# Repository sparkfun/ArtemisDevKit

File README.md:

SparkFun Artemis Development Kit
========================================

* [*SparkFun Artemis Development Kit (DEV-16828)*](https://www.sparkfun.com/products/16828)
* [*SparkFun Artemis Development Kit with Camera (KIT-17071)*](https://www.sparkfun.com/products/17071)

The [*SparkFun Artemis Development Kit (DEV-16828)*](https://www.sparkfun.com/products/16828) is the latest board to be released around the SparkFun Artemis Module and it allows access to more software development features than previous Artemis based boards. Recommended software used to program the Artemis DK are the Arduino IDE, Arm® Mbed™ OS (Studio and CLI), and AmbiqSDK. An updated USB interface (MKL26Z128VFM4 Arm® Cortex®-M0+ MCU, from NXP) allows the Artemis Dev Kit to act as:

* Mass Storage Device (MSD): Used to provide drag and drop programming to the Artemis Module.
* Human Interface Device (HID): Used for the debugging interface to the Artemis Module.
* Communication Port (COM): Used to provide a serial communication UART between the Artemis and the USB connection (PC).

Repository Contents
-------------------

* **/Hardware**
   * Eagle design files (.brd, .sch)
   * Dimensions (.pdf and .png)
   * **/Production** - Production panel files (.brd)
* **/Reference**
   * Datasheets (.pdf)
   * Functional Block Digaram (.png)

Documentation
--------------
* [Hardware Getting Started Guide](https://learn.sparkfun.com/tutorials/1198) - Basic Hardware Guide for the Artemis DK
* Software Guides:
    * [Artemis Development with the Arduino IDE](https://learn.sparkfun.com/tutorials/artemis-development-with-the-arduino-ide) - A software guide for developing with the Artemis module (and related boards) in the Arduino IDE
    * [Artemis Development with Arm&reg; Mbed&trade; OS (Beta)](https://learn.sparkfun.com/tutorials/artemis-development-on-arm-mbed-os-beta) - A software pre-release guide to get started developing in with Mbed&trade; OS
    * Artemis Development with Arm&reg; Mbed&trade; OS (Pending release)
    * [Artemis Development with the AmbiqSDK](https://learn.sparkfun.com/tutorials/using-sparkfun-edge-board-with-ambiq-apollo3-sdk) - A software guide for utilizing the SparkFun Edge board with the AmbiqSDK
* [GitHub Repository for Apollo3 Board Support Packages (BSP)](https://github.com/sparkfun/SparkFun_Apollo3_AmbiqSuite_BSPs) - The Board Support Packages (BSPs) for SparkFun Apollo3 (Artemis) based boards to be used in the AmbiqSuite SDK
    * [ DAPLink Bootloader: `kl26z_artemis_dk_if.bin`](https://github.com/sparkfun/SparkFun_Apollo3_AmbiqSuite_BSPs/raw/master/artemis_dk/intfc/kl26z_bl.bin) - Underlying *bootloader* firmware for the MKL26Z MCU
    * [DAPLink Interface Firmware: `kl26z_bl.bin`](https://github.com/sparkfun/SparkFun_Apollo3_AmbiqSuite_BSPs/raw/master/artemis_dk/intfc/kl26z_artemis_dk_if.bin) - The accompanying *interface firmware* for the DAPLink debug probes from the MKL26Z to the target Artemis Module
* Development Software:
    * [SparkFun Ambiq Apollo3 Arduino Core](https://github.com/sparkfun/Arduino_Apollo3) - The SparkFun Arduino core for the Apollo3 MCU (i.e. the Artemis modules)
        * `.json` file needed for the SparkFun Ambiq Apollo3 Arduino Core:
        <br>
            <code><a href="https://raw.githubusercontent.com/sparkfun/Arduino_Apollo3/master/package_sparkfun_apollo3_index.json">https://raw.githubusercontent.com/sparkfun/Arduino_Apollo3/master/package_sparkfun_apollo3_index.json</a></code>
    * [Mbed™ OS](https://github.com/sparkfun/mbed-os-ambiq-apollo3) - Implementation of the Apollo3 (i.e. Artemis module) in Mbed&trade; OS
    * [AmbiqSDK](https://github.com/sparkfun/AmbiqSuiteSDK) - A copy of the AmbiqSuite SDK maintained by SparkFun
    * [pyOCD](https://github.com/sparkfun/pyOCD) - Implementation of the Apollo3 (i.e. Artemis module) for pyOCD
* Arduino Libraries:
    * [SparkFun LIS2DH12 Arduino Library](https://github.com/sparkfun/SparkFun_LIS2DH12_Arduino_Library) - The Arduino library for the accelerometer
    * [ArduinoBLE Library](https://github.com/arduino-libraries/ArduinoBLE) - The Arduino library for the BLE support

Product Versions
----------------
* [*SparkFun Artemis Development Kit with Camera (KIT-17071)*](https://www.sparkfun.com/products/17071) - v1.0 Initial Release *(kitted with Himax Camera)*
* [*SparkFun Artemis Development Kit (DEV-16828)*](https://www.sparkfun.com/products/16828) - v1.0 Initial Release

License Information
-------------------

This product is _**open source**_! 

Please review the LICENSE.md file for license information. 

If you have any questions or concerns on licensing, please contact technical support on our [SparkFun forums](https://forum.sparkfun.com/viewforum.php?f=152).

Distributed as-is; no warranty is given.

- Your friends at SparkFun.

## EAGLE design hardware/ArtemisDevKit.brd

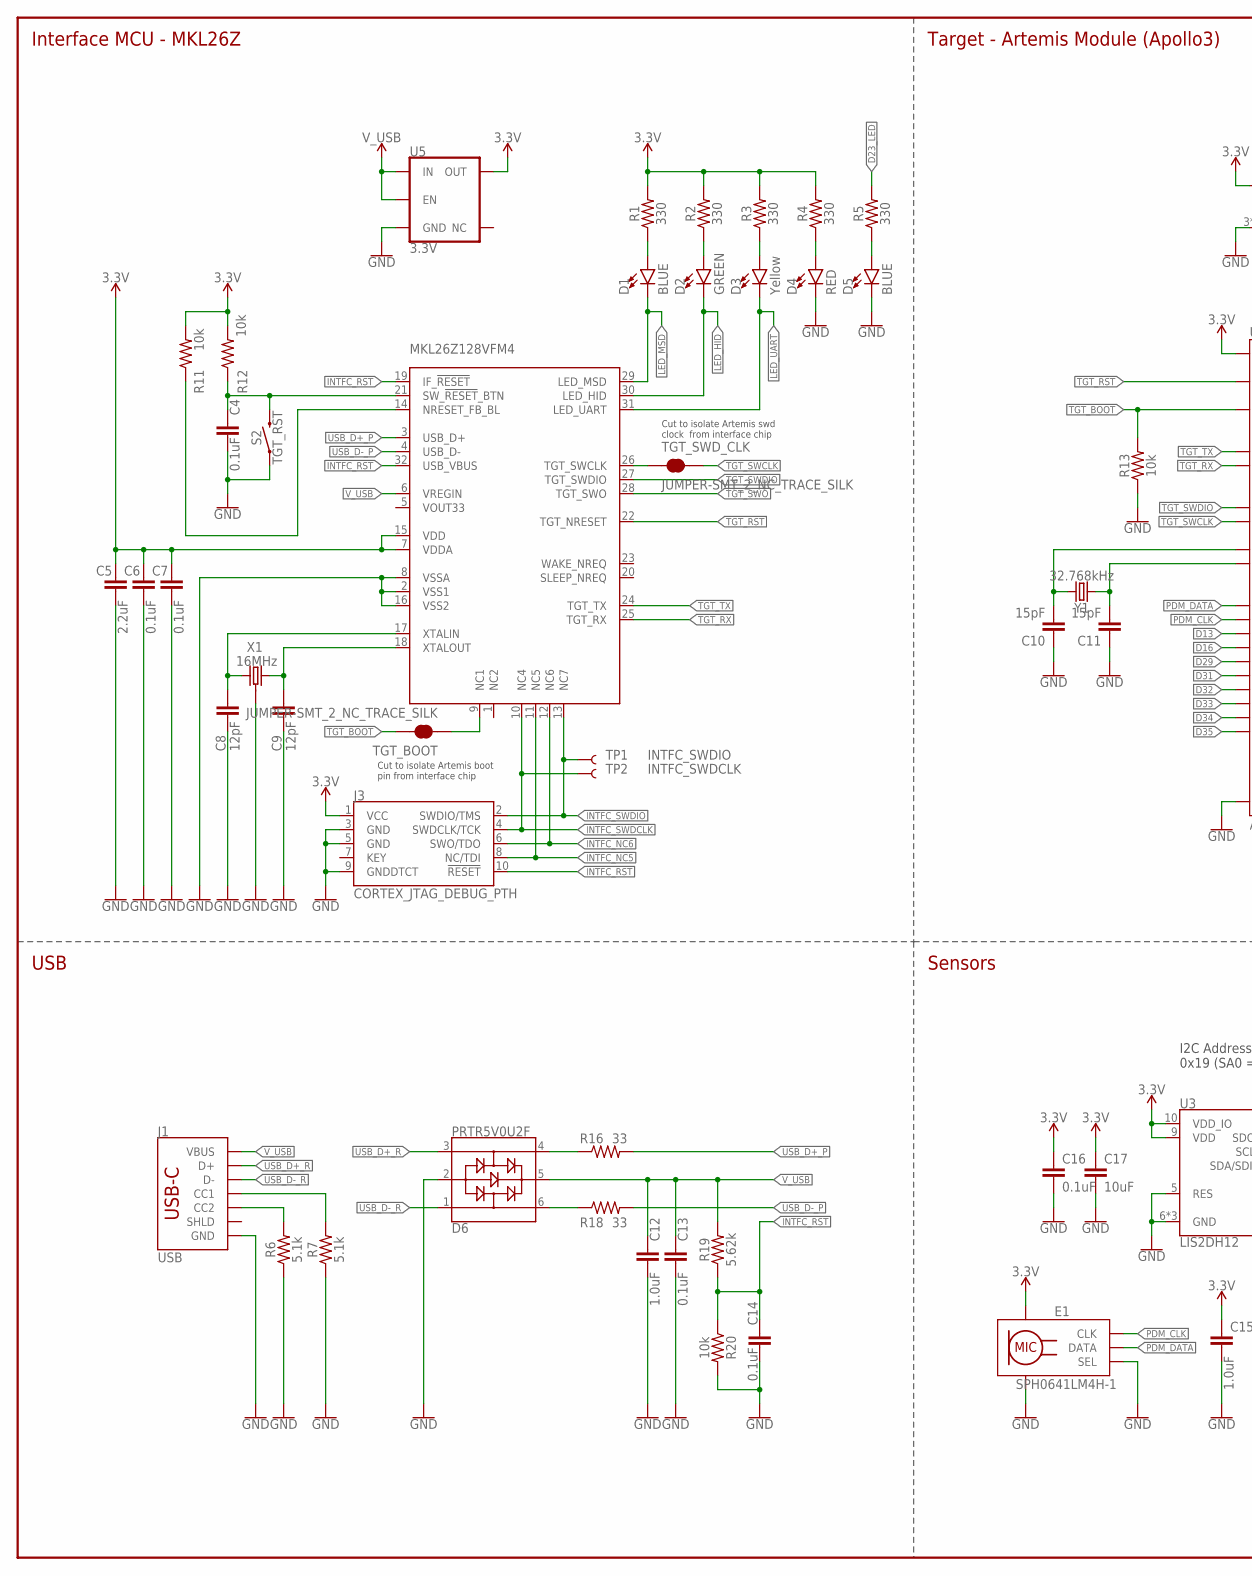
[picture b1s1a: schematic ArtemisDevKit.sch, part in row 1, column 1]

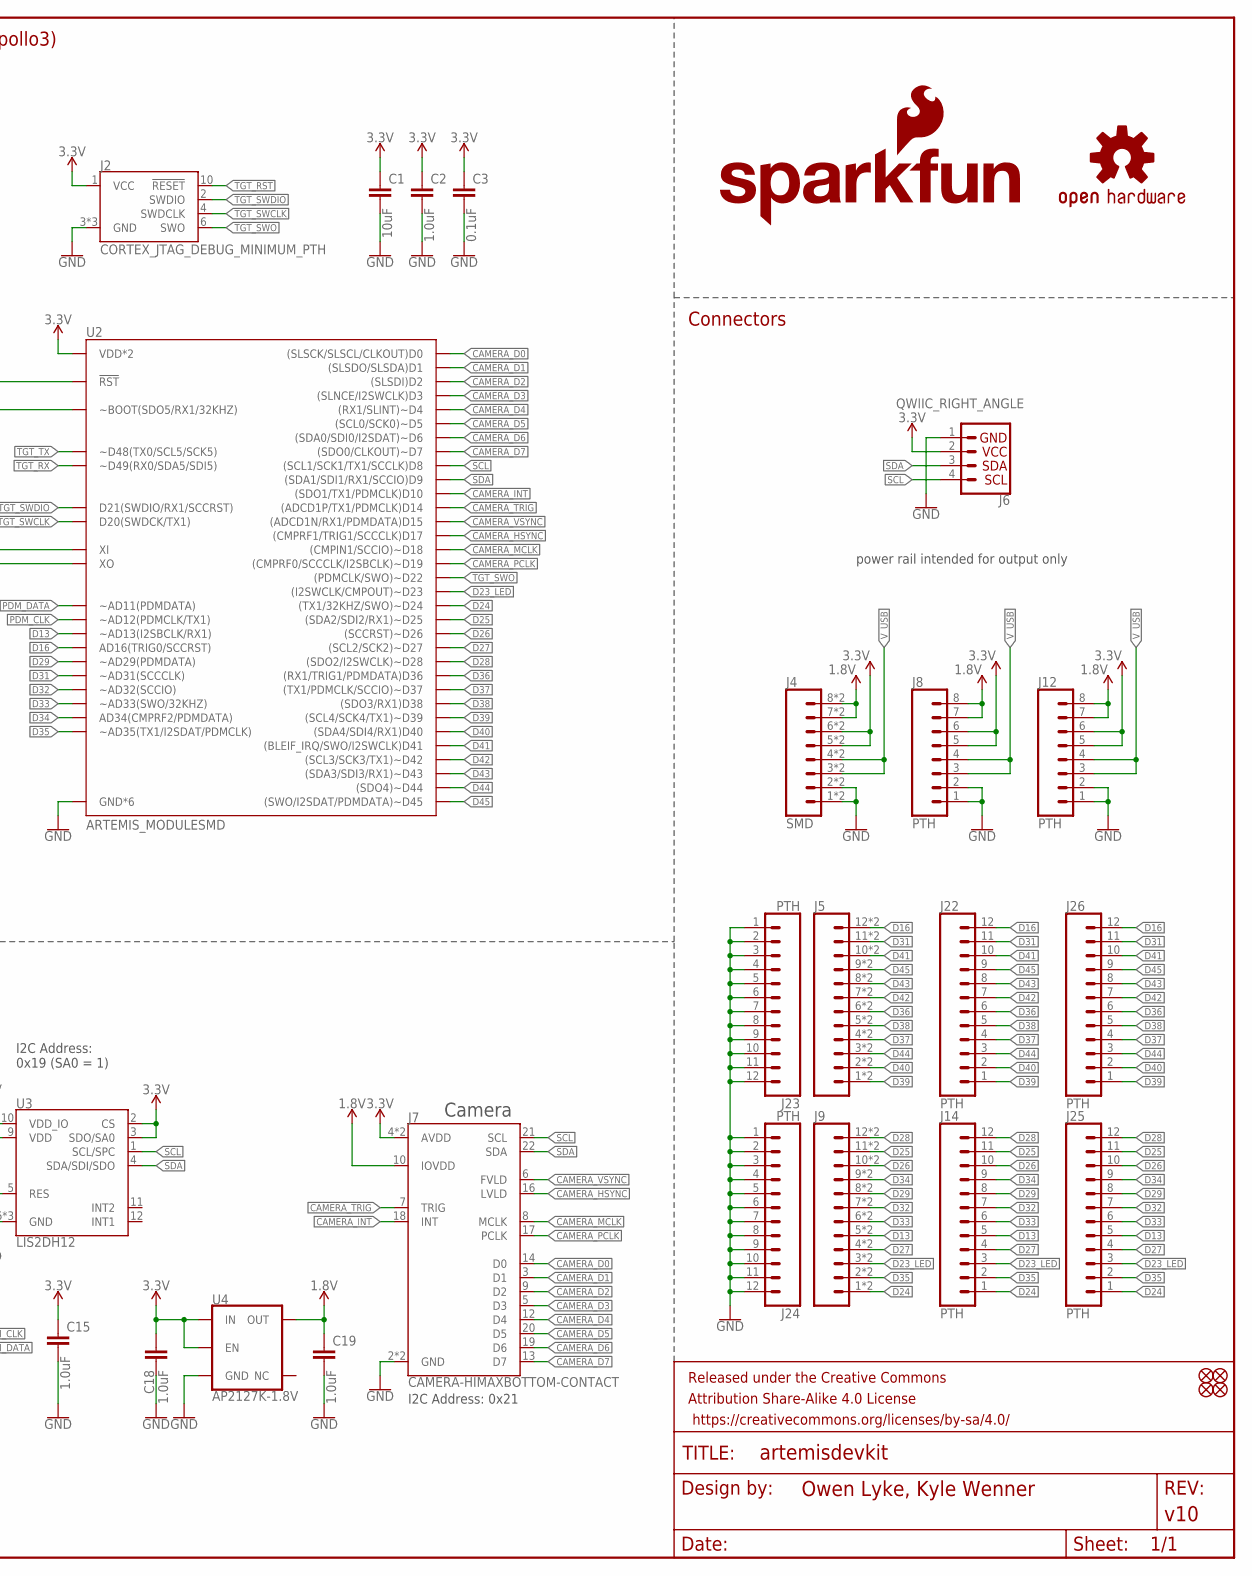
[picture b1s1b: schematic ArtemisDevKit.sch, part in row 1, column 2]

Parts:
C1, C17: 10uF; 0603
C2, C12, C15, C18, C19: 1.0uF; 0603
C3, C4, C6, C7, C13, C14, C16: 0.1uF; 0603
C5: 2.2uF; 0603
C8, C9: 12pF; 0603
C10, C11: 15pF; 0603
D1, D5: BLUE; LED-0603
D2: GREEN; LED-0603
D3: Yellow; LED-0603
D4: RED; LED-0603
D6: PRTR5V0U2F; SOT886
E1: SPH0641LM4H-1; SPH0641LM4H-1_MICROPHONE
FD1, FD2, FD3, FD4: FIDUCIAL1X2; FIDUCIAL-1X2
FRAME1: FRAME-LEDGER; CREATIVE_COMMONS
J1: USB; USB-C-16P
J2: CORTEX_JTAG_DEBUG_MINIMUM_PTH; 2X5-PTH-1.27MM
J3: CORTEX_JTAG_DEBUG_PTH; 2X5-PTH-1.27MM
J4: SMD; 1X08_SMD_COMBINED
J5, J9: CONN_12SMD_COMBINED; 1X12_SMD_COMBINED
J6: QWIIC_RIGHT_ANGLE; JST04_1MM_RA
J7: CAMERA-HIMAXBOTTOM-CONTACT; FPC-24-AMPHENOL-SFV24R-1STE1HLF
J8, J12: PTH; 1X08_NO_SILK
J14, J22, J23, J24, J25, J26: PTH; 1X12_NO_SILK
LOGO1: OSHW-LOGOS; OSHW-LOGO-S
LOGO2: SFE_LOGO_NAME_FLAME.2_INCH; SFE_LOGO_NAME_FLAME_.2
R1, R2, R3, R4, R5: 330; 0603
R6, R7: 5.1k; 0603
R11, R12, R13, R20: 10k; 0603
R16, R18: 33; 0603
R19: 5.62k; 0603
S2: TGT_RST; TACTILE_SWITCH_SMD_5.2MM
TGT_BOOT: JUMPER-SMT_2_NC_TRACE_SILK; SMT-JUMPER_2_NC_TRACE_SILK
TGT_SWD_CLK: JUMPER-SMT_2_NC_TRACE_SILK; SMT-JUMPER_2_NC_TRACE_SILK
TP1: INTFC_SWDIO; PAD.03X.03
TP2: INTFC_SWDCLK; PAD.03X.03
U1: DAPLINK_KL26Z128VFM4; QFN-32-NOPAD
U2: ARTEMIS_MODULESMD; ARTEMIS_FP
U3: LIS2DH12; LGA-12-LISDH12
U4: AP2127K-1.8V; SOT23-5
U5: 3.3V; SOT23-5
X1: 16MHz; CRYSTAL-SMD-2X2.5MM
Y1: 32.768kHz; CRYSTAL-SMD-3.2X1.5MM

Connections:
1.8V: C19.1, J4.7, J4.7@2 (7), J4.8, J4.8@2 (8), J7.10 (IOVDD), J8.7, J8.8, J12.7, J12.8, U4.5 (OUT)
3.3V: C1.1, C2.1, C3.1, C5.1, C6.1, C7.1, C15.1, C16.1, C17.1, C18.1, E1.5 (VDD), J2.1 (VCC), J3.1 (VCC), J4.5, J4.5@2 (5), J4.6, J4.6@2 (6), J6.2, J7.4 (AVDD), J7.11 (AVDD), J8.5, J8.6, J12.5, J12.6, R1.2, R2.2, R3.2, R4.2, R11.2, R12.2, U1.7 (VDDA), U1.15 (VDD), U2.VDD@36 (VDD*2), U2.VDD@37 (VDD*2), U3.2 (CS), U3.3 (SDO/SA0), U3.9 (VDD), U3.10 (VDD_IO), U4.1 (IN), U4.3 (EN), U5.5 (OUT)
!INTFC_RST: C14.1, J3.10 (!RESET), R19.1, R20.1, U1.19 (IF_!RESET), U1.32 (USB_VBUS)
!RST!_BTN: C4.1, R12.1, S2.3 (2), U1.21 (SW_!RESET!_BTN)
!TGT_RST: J2.10 (!RESET), U1.22 (TGT_NRESET), U2.~RST (!RST)
CAMERA_D0: J7.14 (D0), U2.D0 ((SLSCK/SLSCL/CLKOUT)D0)
CAMERA_D1: J7.3 (D1), U2.D1 ((SLSDO/SLSDA)D1)
CAMERA_D2: J7.9 (D2), U2.D2 ((SLSDI)D2)
CAMERA_D3: J7.5 (D3), U2.D3 ((SLNCE/I2SWCLK)D3)
CAMERA_D4: J7.12 (D4), U2.~D4 ((RX1/SLINT)~D4)
CAMERA_D5: J7.20 (D5), U2.~D5 ((SCL0/SCK0)~D5)
CAMERA_D6: J7.19 (D6), U2.~D6 ((SDA0/SDI0/I2SDAT)~D6)
CAMERA_D7: J7.13 (D7), U2.D7 ((SDO0/CLKOUT)~D7)
CAMERA_HSYNC: J7.16 (LVLD), U2.D17 ((CMPRF1/TRIG1/SCCCLK)D17)
CAMERA_INT: J7.18 (INT), U2.D10 ((SDO1/TX1/PDMCLK)D10)
CAMERA_MCLK: J7.8 (MCLK), U2.~D18 ((CMPIN1/SCCIO)~D18)
CAMERA_PCLK: J7.17 (PCLK), U2.~D19 ((CMPRF0/SCCCLK/I2SBCLK)~D19)
CAMERA_TRIG: J7.7 (TRIG), U2.D14 ((ADCD1P/TX1/PDMCLK)D14)
CAMERA_VSYNC: J7.6 (FVLD), U2.D15 ((ADCD1N/RX1/PDMDATA)D15)
D13: J9.5, J9.5@2 (5), J14.5, J25.5, U2.~AD13 (~AD13(I2SBCLK/RX1))
D16: J5.12, J5.12@2 (12), J22.12, J26.12, U2.AD16 (AD16(TRIG0/SCCRST))
D23_LED: J9.3, J9.3@2 (3), J14.3, J25.3, R5.2, U2.~D23 ((I2SWCLK/CMPOUT)~D23)
D24: J9.1, J9.1@2 (1), J14.1, J25.1, U2.~D24 ((TX1/32KHZ/SWO)~D24)
D25: J9.11, J9.11@2 (11), J14.11, J25.11, U2.~D25 ((SDA2/SDI2/RX1)~D25)
D26: J9.10, J9.10@2 (10), J14.10, J25.10, U2.~D26 ((SCCRST)~D26)
D27: J9.4, J9.4@2 (4), J14.4, J25.4, U2.~D27 ((SCL2/SCK2)~D27)
D28: J9.12, J9.12@2 (12), J14.12, J25.12, U2.~D28 ((SDO2/I2SWCLK)~D28)
D29: J9.8, J9.8@2 (8), J14.8, J25.8, U2.~AD29 (~AD29(PDMDATA))
D31: J5.11, J5.11@2 (11), J22.11, J26.11, U2.~AD31 (~AD31(SCCCLK))
D32: J9.7, J9.7@2 (7), J14.7, J25.7, U2.~AD32 (~AD32(SCCIO))
D33: J9.6, J9.6@2 (6), J14.6, J25.6, U2.~AD33/SWO (~AD33(SWO/32KHZ))
D34: J9.9, J9.9@2 (9), J14.9, J25.9, U2.AD34 (AD34(CMPRF2/PDMDATA))
D35: J9.2, J9.2@2 (2), J14.2, J25.2, U2.~AD35 (~AD35(TX1/I2SDAT/PDMCLK))
D36: J5.6, J5.6@2 (6), J22.6, J26.6, U2.D36 ((RX1/TRIG1/PDMDATA)D36)
D37: J5.4, J5.4@2 (4), J22.4, J26.4, U2.~D37 ((TX1/PDMCLK/SCCIO)~D37)
D38: J5.5, J5.5@2 (5), J22.5, J26.5, U2.D38 ((SDO3/RX1)D38)
D39: J5.1, J5.1@2 (1), J22.1, J26.1, U2.~D39 ((SCL4/SCK4/TX1)~D39)
D40: J5.2, J5.2@2 (2), J22.2, J26.2, U2.D40 ((SDA4/SDI4/RX1)D40)
D41: J5.10, J5.10@2 (10), J22.10, J26.10, U2.D41 ((BLEIF_IRQ/SWO/I2SWCLK)D41)
D42: J5.7, J5.7@2 (7), J22.7, J26.7, U2.~D42 ((SCL3/SCK3/TX1)~D42)
D43: J5.8, J5.8@2 (8), J22.8, J26.8, U2.~D43 ((SDA3/SDI3/RX1)~D43)
D44: J5.3, J5.3@2 (3), J22.3, J26.3, U2.~D44 ((SDO4)~D44)
D45: J5.9, J5.9@2 (9), J22.9, J26.9, U2.~D45 ((SWO/I2SDAT/PDMDATA)~D45)
GND: C1.2, C2.2, C3.2, C4.2, C5.2, C6.2, C7.2, C8.2, C9.2, C10.1, C11.1, C12.2, C13.2, C14.2, C15.2, C16.2, C17.2, C18.2, C19.2, D4.C, D5.C, D6.2, E1.2 (SEL), E1.3 (GND), E1.6 (GND), E1.7 (GND), E1.8 (GND), J1.GND, J1.GND2 (GND), J2.3 (GND), J2.5 (GND), J2.9 (GND), J3.3 (GND), J3.5 (GND), J3.9 (GNDDTCT), J4.1, J4.1@2 (1), J4.2, J4.2@2 (2), J6.1, J7.2 (GND), J7.15 (GND), J8.1, J8.2, J12.1, J12.2, J23.1, J23.2, J23.3, J23.4, J23.5, J23.6, J23.7, J23.8, J23.9, J23.10, J23.11, J23.12, J24.1, J24.2, J24.3, J24.4, J24.5, J24.6, J24.7, J24.8, J24.9, J24.10, J24.11, J24.12, R6.1, R7.1, R13.1, R20.2, S2.1, U1.2 (VSS1), U1.8 (VSSA), U1.16 (VSS2), U2.GND@1 (GND*6), U2.GND@22 (GND*6), U2.GND@38 (GND*6), U2.GND@39 (GND*6), U2.GND@47 (GND*6), U2.GND@59 (GND*6), U3.5 (RES), U3.6 (GND), U3.7 (GND), U3.8 (GND), U4.2 (GND), U5.2 (GND), X1.P2 (GND), X1.P4 (GND)
INTFC_NC5: J3.8 (NC/TDI), U1.11 (NC5)
INTFC_NC6: J3.6 (SWO/TDO), U1.12 (NC6)
INTFC_SWDCLK: J3.4 (SWDCLK/TCK), TP2.P$1, U1.10 (NC4)
INTFC_SWDIO: J3.2 (SWDIO/TMS), TP1.P$1, U1.13 (NC7)
LED_HID: D2.C, U1.30 (LED_HID)
LED_MSD: D1.C, U1.29 (LED_MSD)
LED_UART: D3.C, U1.31 (LED_UART)
unnamed: D1.A, R1.1
unnamed: D2.A, R2.1
unnamed: D3.A, R3.1
unnamed: J1.B5 (CC2), R6.2
unnamed: J1.A5 (CC1), R7.2
unnamed: D5.A, R5.1
unnamed: D4.A, R4.1
unnamed: D6.4, R16.1
unnamed: D6.6, R18.1
unnamed: R11.1, U1.14 (NRESET_FB_BL)
unnamed: TGT_SWD_CLK.1, U1.26 (TGT_SWCLK)
unnamed: C8.1, U1.17 (XTALIN), X1.P1 (1)
unnamed: C10.2, U2.XI, Y1.P$2 (2)
unnamed: C11.2, U2.XO, Y1.P$1 (1)
unnamed: C9.1, U1.18 (XTALOUT), X1.P3 (2)
unnamed: TGT_BOOT.1, U1.9 (NC1)
PDM_CLK: E1.4 (CLK), U2.~AD12 (~AD12(PDMCLK/TX1))
PDM_DATA: E1.1 (DATA), U2.~AD11 (~AD11(PDMDATA))
SCL: J6.4, J7.21 (SCL), U2.D8 ((SCL1/SCK1/TX1/SCCLK)D8), U3.1 (SCL/SPC)
SDA: J6.3, J7.22 (SDA), U2.D9 ((SDA1/SDI1/RX1/SCCIO)D9), U3.4 (SDA/SDI/SDO)
TGT_BOOT: R13.2, TGT_BOOT.2, U2.BOOT (~BOOT(SDO5/RX1/32KHZ))
TGT_RX: U1.25 (TGT_RX), U2.RXI-0 (~D49(RX0/SDA5/SDI5))
TGT_SWCLK: J2.4 (SWDCLK), TGT_SWD_CLK.2, U2.SWDCK (D20(SWDCK/TX1))
TGT_SWDIO: J2.2 (SWDIO), U1.27 (TGT_SWDIO), U2.SWDIO (D21(SWDIO/RX1/SCCRST))
TGT_SWO: J2.6 (SWO), U1.28 (TGT_SWO), U2.~D22 ((PDMCLK/SWO)~D22)
TGT_TX: U1.24 (TGT_TX), U2.TXO-0 (~D48(TX0/SCL5/SCK5))
USB_D+_P: R16.2, U1.3 (USB_D+)
USB_D+_R: D6.3, J1.A6 (D+), J1.B6 (D+)
USB_D-_P: R18.2, U1.4 (USB_D-)
USB_D-_R: D6.1, J1.A7 (D-), J1.B7 (D-)
V_USB: C12.1, C13.1, D6.5, J1.VBUS1 (VBUS), J1.VBUS2 (VBUS), J4.3, J4.3@2 (3), J4.4, J4.4@2 (4), J8.3, J8.4, J12.3, J12.4, R19.2, U1.6 (VREGIN), U5.1 (IN), U5.3 (EN)

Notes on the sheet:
I2C Address: 0x21
Camera
I2C Address: 0x19 (SA0 = 1)
Interface MCU - MKL26Z
Target - Artemis Module (Apollo3)
Connectors
USB
Sensors
Cut to isolate Artemis boot pin from interface chip
Cut to isolate Artemis swd clock from interface chip
power rail intended for output only

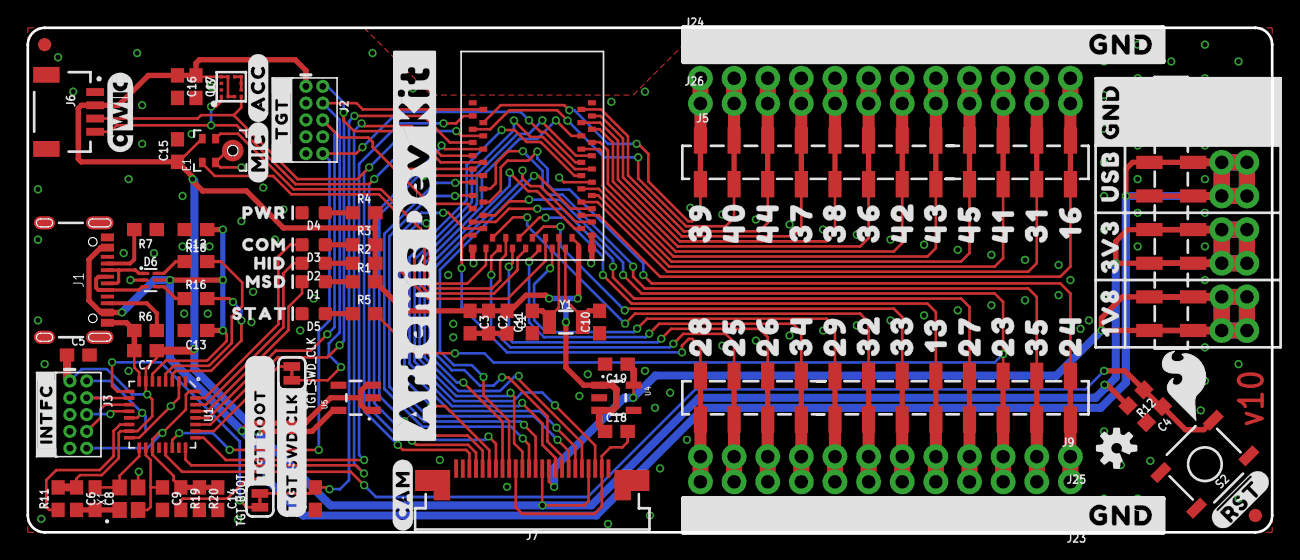
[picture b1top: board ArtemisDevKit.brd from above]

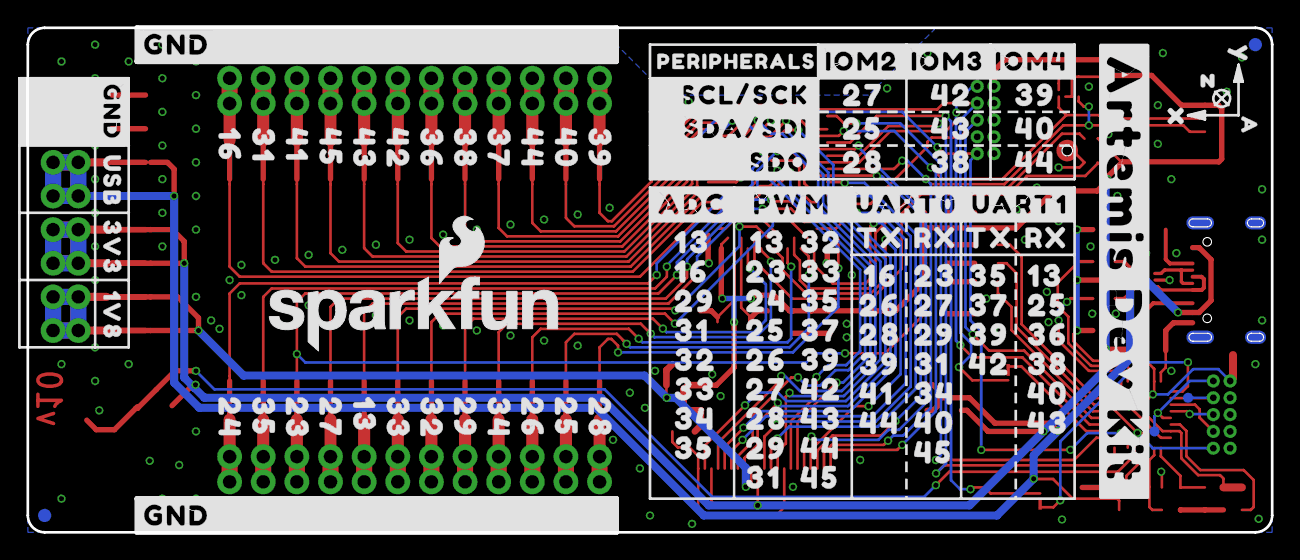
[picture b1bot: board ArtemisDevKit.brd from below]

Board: 2 copper layers, 94.0 x 38.1 mm, 229 parts (113 on the bottom side), 82 nets.

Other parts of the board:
U$1, U$2: #GND#10
U$3, U$132: 15_#GND#
U$4, U$129: 16_1V8
U$5, U$130: 17_3V3
U$6, U$131: 18_USB
U$7, U$64, U$98, U$147: 33_16
U$8, U$73, U$97, U$149, U$154: 41_31
U$9, U$68, U$96: 51_41
U$10, U$55, U$76, U$163: 55_45
U$11, U$54, U$86, U$91, U$161: 53_43
U$12, U$53, U$80, U$90, U$160: 52_42
U$13, U$52, U$83: 46_36
U$14, U$51, U$84, U$92: 48_38
U$15, U$50, U$78, U$158: 47_37
U$16, U$49, U$69, U$95, U$162: 54_44
U$17, U$48, U$75, U$85, U$94: 50_40
U$18, U$47, U$67, U$79, U$93, U$159: 49_39
U$19, U$58, U$110: 35_24
U$20, U$77, U$109, U$153, U$157: 45_35
U$21, U$57, U$70, U$108: 34_23
U$22, U$61, U$71, U$87, U$107: 38_27
U$23, U$56, U$81, U$106, U$146: 32_13
U$24, U$105, U$151, U$156: 43_33
U$25, U$104, U$150, U$155: 42_32
U$26, U$63, U$72, U$103, U$148: 40_29
U$27, U$74, U$102, U$152: 44_34
U$28, U$60, U$65, U$101: 37_26
U$29, U$59, U$82, U$88, U$100: 36_25
U$30, U$62, U$66, U$89, U$99: 39_28
U$31: 19_#IOM2#
U$32: QWIIC_6MM
U$33: 20_#IOM3#
U$34: 21_#IOM4#
U$35: #TGT#3
U$36: #ARTEMIS_DEV_KIT#0
U$37: #SCL#SCK#23
U$38: 30_#PWM#
U$39: 29_#ADC#
U$40: 25_#UART0#
U$41: 26_#UART1#
U$42, U$43: 27_TX
U$44, U$46: 28_RX
U$45: SFE_LOGO_FLAME_.2
U$111: #SDA#SDI#24
U$112: #SDO#25
U$113: 14_A
U$114: 15_X
U$115: 16_Y
U$116: 17_Z
U$117: 7_COM
U$118: 8_HID
U$119: 9_MSD
U$120: 10_STAT
U$121: 6_PWR
U$122: #ARTEMIS_DEV_KIT#1
U$123: #INTFC#2
U$124: #TGT_BOOT#4
U$125: #TGT_SWD_CLK#5
U$126: #CAM#13
U$137: #MIC#11
U$138: #ACC#12
U$140, U$141: 14_#GND#
U$142: ##RST##18
U$145: 19_PERIPHERALS

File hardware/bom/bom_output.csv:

Qty, PROD_ID, Names, Value, Package
2, CAP-11015, C1; C17, 10uF, 0603
5, CAP-00868, C2; C12; C15; C18; C19, 1.0uF, 0603
7, CAP-08604, C3; C4; C6; C7; C13; C14; C16, 0.1uF, 0603
1, CAP-07888, C5, 2.2uF, 0603
2, CAP-09137, C8; C9, 12pF, 0603
2, CAP-07881, C10; C11, 15pF, 0603
2, DIO-08575, D1; D5, BLUE, LED-0603
1, DIO-00821, D2, GREEN, LED-0603
1, DIO-09003, D3, Yellow, LED-0603
1, DIO-00819, D4, RED, LED-0603
1, DIO-14084, D6, PRTR5V0U2F, SOT886
1, IC-14361, E1, SPH0641LM4H-1, SPH0641LM4H-1_MICROPHONE
1, CONN-14122, J1, , USB-C-16P
1, , J2, CORTEX_JTAG_DEBUG_MINIMUM_PTH, 2X5-PTH-1.27MM
1, , J3, CORTEX_JTAG_DEBUG_PTH, 2X5-PTH-1.27MM
3, CONN-10204, J4; J10; J11, , 1X08_SMD_COMBINED
2, CONN-08511, J5; J9, 1X04_SMD_STRAIGHT_COMBO, 1X04_SMD_VERTICAL_COMBO
1, CONN-13694, J6, QWIIC_RIGHT_ANGLE, JST04_1MM_RA
1, CONN-14233, J7, CAMERA-HIMAX, FPC-24-AMPHENOL-SFV24R-1STE1HLF
2, CONN-08438, J8; J12, , 1X08_NO_SILK
5, RES-00818, R1; R2; R3; R4; R5, 330, 0603
2, RES-12083, R6; R7, 5.1k, 0603
4, RES-00824, R11; R12; R13; R20, 10k, 0603
2, RES-08272, R14; R15, 2.2k, 0603
2, RES-08270, R16; R18, 33, 0603
1, RES-12581, R17, 10, 0603
1, RES-09823, R19, 5.62k, 0603
1, SWCH-12418, S1, DIP-04SMD, DIPSWITCH-04-SMD
1, SWCH-13065, S2, TGT_RST, TACTILE_SWITCH_SMD_4.6X2.8MM
1, , U1, DAPLINK_KL26Z, QFN-32-NOPAD
1, SUB-14402, U2, ARTEMIS_MODULESMD, ARTEMIS_FP
1, IC-14229, U3, LIS2DH12, LGA-12-LISDH12
1, VREG-14239, U4, AP2127K-1.8V, SOT23-5
1, XTAL-14664, X1, 16MHz, CRYSTAL-SMD-2X2.5MM
1, XTAL-13062, Y1, 32.768kHz, CRYSTAL-SMD-3.2X1.5MM

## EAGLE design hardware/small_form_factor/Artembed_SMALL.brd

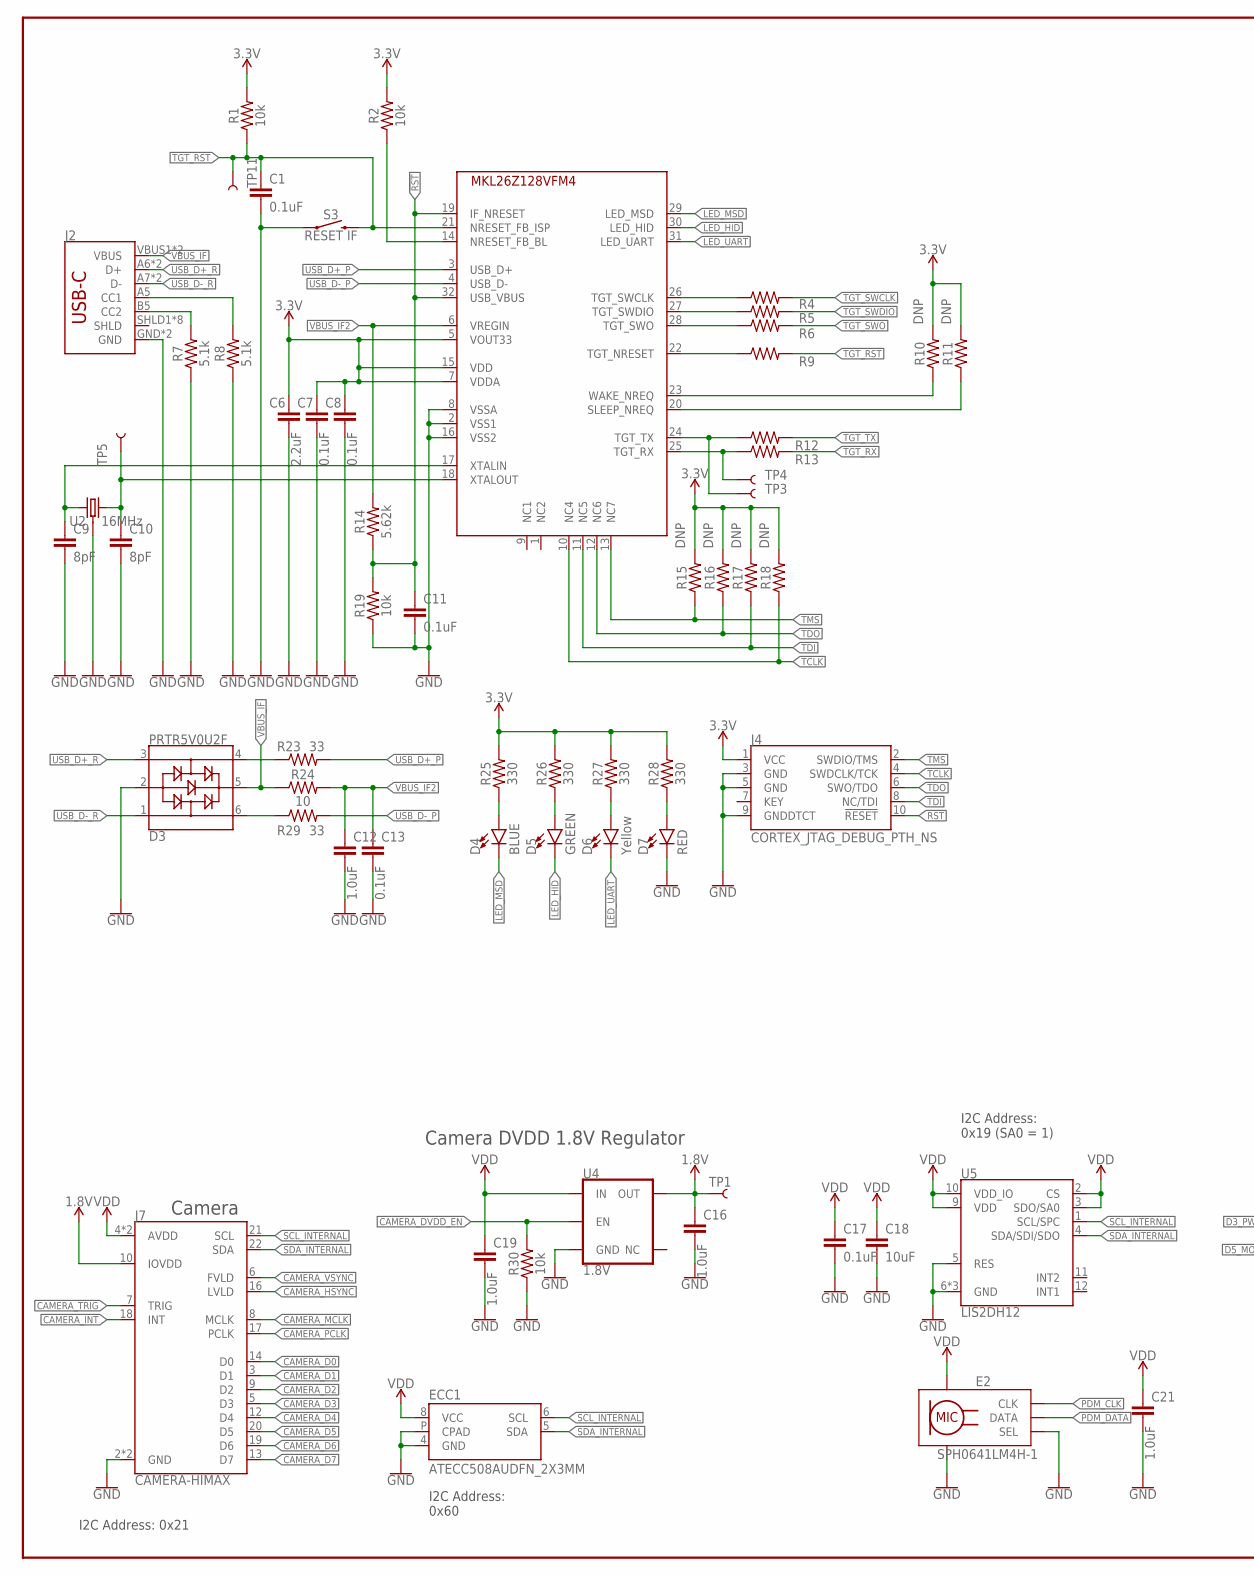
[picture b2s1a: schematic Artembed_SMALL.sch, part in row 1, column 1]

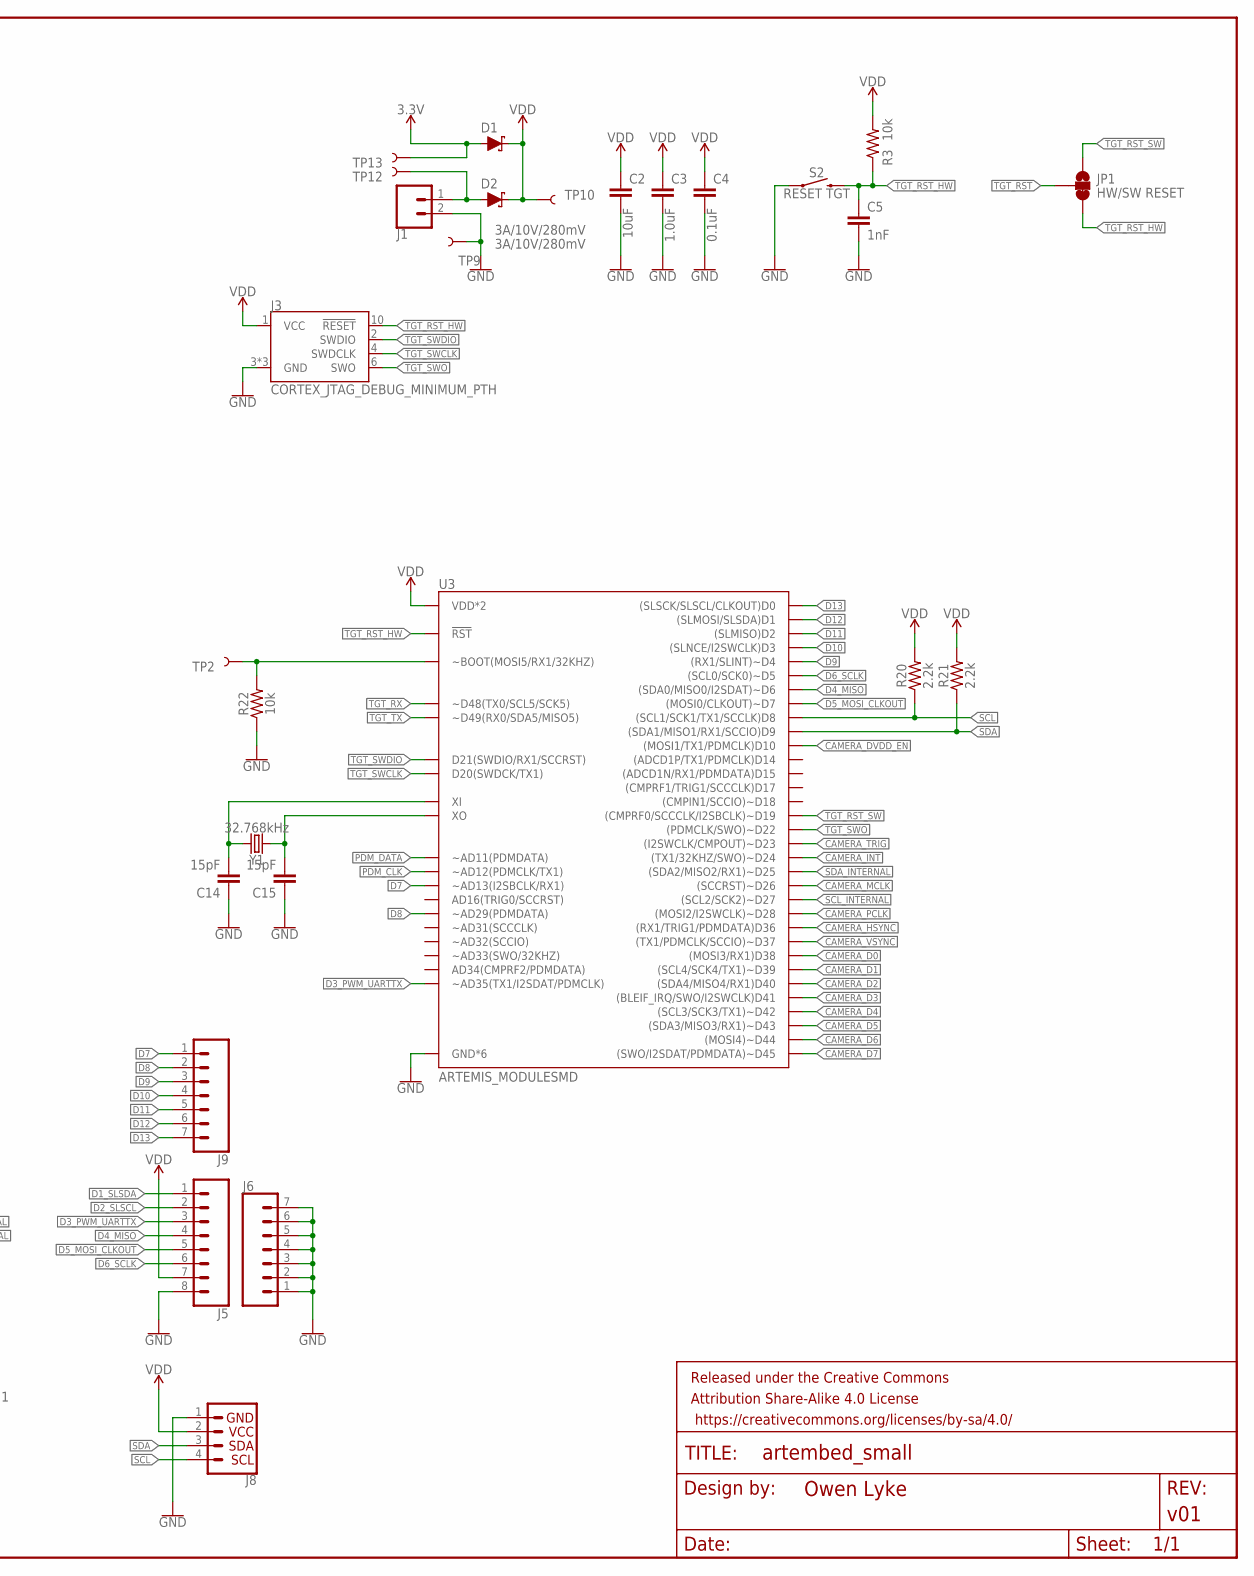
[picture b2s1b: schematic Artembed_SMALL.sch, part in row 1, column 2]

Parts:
C1, C4, C7, C8, C11, C13, C17: 0.1uF; 0603
C2, C18: 10uF; 0603
C3, C12, C16, C19, C21: 1.0uF; 0603
C5: 1nF; 0603
C6: 2.2uF; 0603
C9, C10: 8pF; 0603
C14, C15: 15pF; 0603
D1, D2: 3A/10V/280mV; SOD-323
D3: PRTR5V0U2F; SOT886
D4: BLUE; LED-0603
D5: GREEN; LED-0603
D6: Yellow; LED-0603
D7: RED; LED-0603
E2: SPH0641LM4H-1; SPH0641LM4H-1_MICROPHONE
ECC1: ATECC508AUDFN_2X3MM; UDFN_2X3MM
FRAME1: FRAME-LEDGER; CREATIVE_COMMONS
J1: CONN_02-JST-2MM-SMT; JST-2-SMD
J2: USB_C2-LAYER; USB-C-16P
J3: CORTEX_JTAG_DEBUG_MINIMUM_PTH; 2X5-PTH-1.27MM
J4: CORTEX_JTAG_DEBUG_PTH_NS; 2X5-PTH-1.27MM-NO_SILK
J5: CONN_08NO_SILK_FEMALE_PTH; 1X08_NO_SILK
J6, J9: CONN_07NO_SILK; 1X07_NO_SILK
J7: CAMERA-HIMAX; FPC-24-AMPHENOL-SFV24R-1STE1HLF
J8: QWIIC_CONNECTORJS-1MM; JST04_1MM_RA
JP1: HW/SW RESET; SMT-JUMPER_3_1-NC_TRACE_SILK
R1, R2, R3, R19, R22, R30: 10k; 0603
R4, R5, R6, R9, R12, R13: 0; 0603
R7, R8: 5.1k; 0603
R10, R11, R15, R16, R17, R18: DNP; 0603
R14: 5.62k; 0603
R20, R21: 2.2k; 0603
R23, R29: 33; 0603
R24: 10; 0603
R25, R26, R27, R28: 330; 0603
S2: RESET TGT; TACTILE_SWITCH_SMD_4.6X2.8MM
S3: RESET IF; TACTILE_SWITCH_SMD_4.6X2.8MM
TP1, TP2, TP3, TP4, TP5, TP9, TP10, TP11, TP12, TP13: TEST-POINT3X5; PAD.03X.05
U1: DAPLINK_KL26Z; QFN-32-NOPAD
U2: 16MHz; CRYSTAL-SMD-3.2X2.5MM
U3: ARTEMIS_MODULESMD; ARTEMIS_FP
U4: 1.8V; SOT23-5
U5: LIS2DH12; LGA-12-LISDH12
Y1: 32.768kHz; CRYSTAL-SMD-3.2X1.5MM

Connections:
1.8V: C16.1, J7.10 (IOVDD), TP1.P$1, U4.5 (OUT)
3.3V: C6.1, C7.1, C8.1, D1.A, J4.1 (VCC), R1.2, R2.2, R10.2, R11.2, R15.2, R16.2, R17.2, R18.2, R25.2, R26.2, R27.2, R28.2, TP13.P$1, U1.5 (VOUT33), U1.7 (VDDA), U1.15 (VDD)
!RST: C11.1, J4.10 (!RESET), R14.1, R19.2, U1.19 (IF_NRESET), U1.32 (USB_VBUS)
!TGT_RST: C1.1, JP1.2, R1.1, R9.2, S3.3 (2), S3.4 (2), TP11.P$1, U1.21 (NRESET_FB_ISP)
!TGT_RST!_HW: C5.1, J3.10 (!RESET), JP1.3, R3.1, S2.3 (2), S2.4 (2), U3.~RST (!RST)
!TGT_RST!_SW: JP1.1, U3.~D19 ((CMPRF0/SCCCLK/I2SBCLK)~D19)
CAMERA_D0: J7.14 (D0), U3.D38 ((MOSI3/RX1)D38)
CAMERA_D1: J7.3 (D1), U3.~D39 ((SCL4/SCK4/TX1)~D39)
CAMERA_D2: J7.9 (D2), U3.D40 ((SDA4/MISO4/RX1)D40)
CAMERA_D3: J7.5 (D3), U3.D41 ((BLEIF_IRQ/SWO/I2SWCLK)D41)
CAMERA_D4: J7.12 (D4), U3.~D42 ((SCL3/SCK3/TX1)~D42)
CAMERA_D5: J7.20 (D5), U3.~D43 ((SDA3/MISO3/RX1)~D43)
CAMERA_D6: J7.19 (D6), U3.~D44 ((MOSI4)~D44)
CAMERA_D7: J7.13 (D7), U3.~D45 ((SWO/I2SDAT/PDMDATA)~D45)
CAMERA_DVDD_EN: R30.2, U3.D10 ((MOSI1/TX1/PDMCLK)D10), U4.3 (EN)
CAMERA_HSYNC: J7.16 (LVLD), U3.D36 ((RX1/TRIG1/PDMDATA)D36)
CAMERA_INT: J7.18 (INT), U3.~D24 ((TX1/32KHZ/SWO)~D24)
CAMERA_MCLK: J7.8 (MCLK), U3.~D26 ((SCCRST)~D26)
CAMERA_PCLK: J7.17 (PCLK), U3.~D28 ((MOSI2/I2SWCLK)~D28)
CAMERA_TRIG: J7.7 (TRIG), U3.~D23 ((I2SWCLK/CMPOUT)~D23)
CAMERA_VSYNC: J7.6 (FVLD), U3.~D37 ((TX1/PDMCLK/SCCIO)~D37)
D1_SLSDA: J5.1
D2_SLSCL: J5.2
D3_PWM_UARTTX: J5.3, U3.~AD35 (~AD35(TX1/I2SDAT/PDMCLK))
D4_MISO: J5.4, U3.~D6 ((SDA0/MISO0/I2SDAT)~D6)
D5_MOSI_CLKOUT: J5.5, U3.D7 ((MOSI0/CLKOUT)~D7)
D6_SCLK: J5.6, U3.~D5 ((SCL0/SCK0)~D5)
D7: J9.1, U3.~AD13 (~AD13(I2SBCLK/RX1))
D8: J9.2, U3.~AD29 (~AD29(PDMDATA))
D9: J9.3, U3.~D4 ((RX1/SLINT)~D4)
D10: J9.4, U3.D3 ((SLNCE/I2SWCLK)D3)
D11: J9.5, U3.D2 ((SLMISO)D2)
D12: J9.6, U3.D1 ((SLMOSI/SLSDA)D1)
D13: J9.7, U3.D0 ((SLSCK/SLSCL/CLKOUT)D0)
GND: C1.2, C2.2, C3.2, C4.2, C5.2, C6.2, C7.2, C8.2, C9.2, C10.2, C11.2, C12.2, C13.2, C14.1, C15.1, C16.2, C17.2, C18.2, C19.2, C21.2, D3.2, D7.C, E2.2 (SEL), E2.3 (GND), E2.6 (GND), E2.7 (GND), E2.8 (GND), ECC1.4 (GND), ECC1.P (CPAD), J1.2 (1), J2.GND, J2.GND2 (GND), J3.3 (GND), J3.5 (GND), J3.9 (GND), J4.3 (GND), J4.5 (GND), J4.9 (GNDDTCT), J5.8, J6.1, J6.2, J6.3, J6.4, J6.5, J6.6, J6.7, J7.2 (GND), J7.15 (GND), J8.1, R7.1, R8.1, R19.1, R22.1, R30.1, S2.1, S2.2 (1), S3.1, S3.2 (1), TP9.P$1, U1.2 (VSS1), U1.8 (VSSA), U1.16 (VSS2), U2.2 (GND), U2.4 (GND), U3.GND@1 (GND*6), U3.GND@22 (GND*6), U3.GND@38 (GND*6), U3.GND@39 (GND*6), U3.GND@47 (GND*6), U3.GND@59 (GND*6), U4.2 (GND), U5.5 (RES), U5.6 (GND), U5.7 (GND), U5.8 (GND)
LED_HID: D5.C, U1.30 (LED_HID)
LED_MSD: D4.C, U1.29 (LED_MSD)
LED_UART: D6.C, U1.31 (LED_UART)
unnamed: D4.A, R25.1
unnamed: D5.A, R26.1
unnamed: D6.A, R27.1
unnamed: J2.B5 (CC2), R7.2
unnamed: J2.A5 (CC1), R8.2
unnamed: D7.A, R28.1
unnamed: D3.4, R23.1
unnamed: D3.6, R29.1
unnamed: R2.1, U1.14 (NRESET_FB_BL)
unnamed: R11.1, U1.20 (SLEEP_NREQ)
unnamed: C9.1, U1.17 (XTALIN), U2.1
unnamed: C14.2, U3.XI, Y1.P$2 (2)
unnamed: C15.2, U3.XO, Y1.P$1 (1)
unnamed: C10.1, TP5.P$1, U1.18 (XTALOUT), U2.3 (2)
unnamed: R12.1, TP3.P$1, U1.24 (TGT_TX)
unnamed: R13.1, TP4.P$1, U1.25 (TGT_RX)
unnamed: R10.1, U1.23 (WAKE_NREQ)
unnamed: R22.2, TP2.P$1, U3.BOOT (~BOOT(MOSI5/RX1/32KHZ))
unnamed: D2.A, J1.1 (2), TP12.P$1
unnamed: R9.1, U1.22 (TGT_NRESET)
unnamed: R4.1, U1.26 (TGT_SWCLK)
unnamed: R5.1, U1.27 (TGT_SWDIO)
unnamed: R6.1, U1.28 (TGT_SWO)
PDM_CLK: E2.4 (CLK), U3.~AD12 (~AD12(PDMCLK/TX1))
PDM_DATA: E2.1 (DATA), U3.~AD11 (~AD11(PDMDATA))
SCL: J8.4, R20.1, U3.D8 ((SCL1/SCK1/TX1/SCCLK)D8)
SCL_INTERNAL: ECC1.6 (SCL), J7.21 (SCL), U3.~D27 ((SCL2/SCK2)~D27), U5.1 (SCL/SPC)
SDA: J8.3, R21.1, U3.D9 ((SDA1/MISO1/RX1/SCCIO)D9)
SDA_INTERNAL: ECC1.5 (SDA), J7.22 (SDA), U3.~D25 ((SDA2/MISO2/RX1)~D25), U5.4 (SDA/SDI/SDO)
TCLK: J4.4 (SWDCLK/TCK), R18.1, U1.10 (NC4)
TDI: J4.8 (NC/TDI), R17.1, U1.11 (NC5)
TDO: J4.6 (SWO/TDO), R16.1, U1.12 (NC6)
TGT_RX: R13.2, U3.TXO-0 (~D48(TX0/SCL5/SCK5))
TGT_SWCLK: J3.4 (SWDCLK), R4.2, U3.SWDCK (D20(SWDCK/TX1))
TGT_SWDIO: J3.2 (SWDIO), R5.2, U3.SWDIO (D21(SWDIO/RX1/SCCRST))
TGT_SWO: J3.6 (SWO), R6.2, U3.~D22 ((PDMCLK/SWO)~D22)
TGT_TX: R12.2, U3.RXI-0 (~D49(RX0/SDA5/MISO5))
TMS: J4.2 (SWDIO/TMS), R15.1, U1.13 (NC7)
USB_D+_P: R23.2, U1.3 (USB_D+)
USB_D+_R: D3.3, J2.A6 (D+), J2.B6 (D+)
USB_D-_P: R29.2, U1.4 (USB_D-)
USB_D-_R: D3.1, J2.A7 (D-), J2.B7 (D-)
VBUS_IF: D3.5, J2.VBUS1 (VBUS), J2.VBUS2 (VBUS), R24.1
VBUS_IF2: C12.1, C13.1, R14.2, R24.2, U1.6 (VREGIN)
VDD: C2.1, C3.1, C4.1, C17.1, C18.1, C19.1, C21.1, D1.C, D2.C, E2.5 (VDD), ECC1.8 (VCC), J3.1 (VCC), J5.7, J7.4 (AVDD), J7.11 (AVDD), J8.2, R3.2, R20.2, R21.2, TP10.P$1, U3.VDD@36 (VDD*2), U3.VDD@37 (VDD*2), U4.1 (IN), U5.2 (CS), U5.3 (SDO/SA0), U5.9 (VDD), U5.10 (VDD_IO)

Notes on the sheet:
Camera DVDD 1.8V Regulator
I2C Address: 0x21
Camera
I2C Address: 0x19 (SA0 = 1)
I2C Address: 0x60

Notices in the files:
parts and their libraries:
SparkFun-Capacitors: Licensing: Creative Commons ShareAlike 4.0 International - https://creativecommons.org/licenses/by-sa/4.0
SparkFun-Aesthetics: Released under the Creative Commons Attribution Share-Alike 4.0 License
SparkFun-Aesthetics: https://creativecommons.org/licenses/by-sa/4.0
